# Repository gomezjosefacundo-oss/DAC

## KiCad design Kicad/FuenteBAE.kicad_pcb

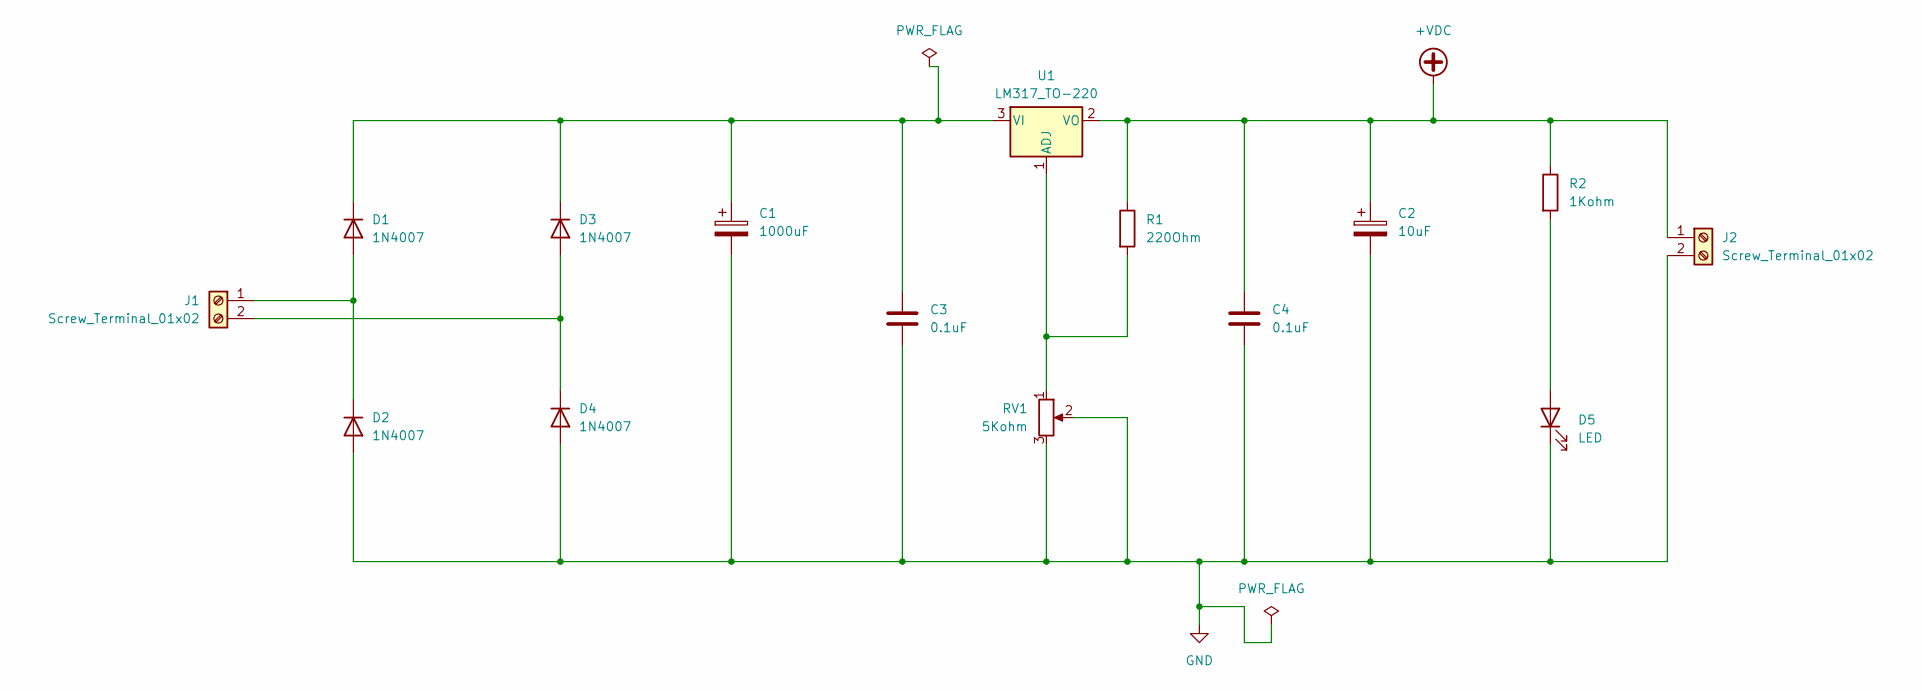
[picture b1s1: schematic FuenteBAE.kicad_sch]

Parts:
C1: 1000uF; CP_Radial_D10.0mm_P2.50mm
C2: 10uF; CP_Radial_D4.0mm_P2.00mm
C3, C4: 0.1uF; C_Disc_D4.7mm_W2.5mm_P5.00mm
D1, D2, D3, D4: 1N4007; D_DO-41_SOD81_P10.16mm_Horizontal
D5: LED; LED_D5.0mm
J1, J2: Screw_Terminal_01x02; Altech_AK300_1x02_P5.00mm_45-Degree
R1: 220Ohm; R_Axial_DIN0207_L6.3mm_D2.5mm_P10.16mm_Horizontal
R2: 1Kohm; R_Axial_DIN0207_L6.3mm_D2.5mm_P10.16mm_Horizontal
RV1: 5Kohm; Potentiometer_Bourns_3296W_Vertical
U1: LM317_TO-220; TO-220-3_Vertical

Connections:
+VDC: C2.1, C4.1, J2.1, R1.1, R2.1, U1.2 (VO)
GND: C1.2, C2.2, C3.2, C4.2, D2.2 (A), D4.2 (A), D5.1 (K), J2.2, RV1.2, RV1.3
unnamed: D1.2 (A), D2.1 (K), J1.1
unnamed: C1.1, C3.1, D1.1 (K), D3.1 (K), U1.3 (VI)
unnamed: D3.2 (A), D4.1 (K), J1.2
unnamed: D5.2 (A), R2.2
unnamed: R1.2, RV1.1, U1.1 (ADJ)

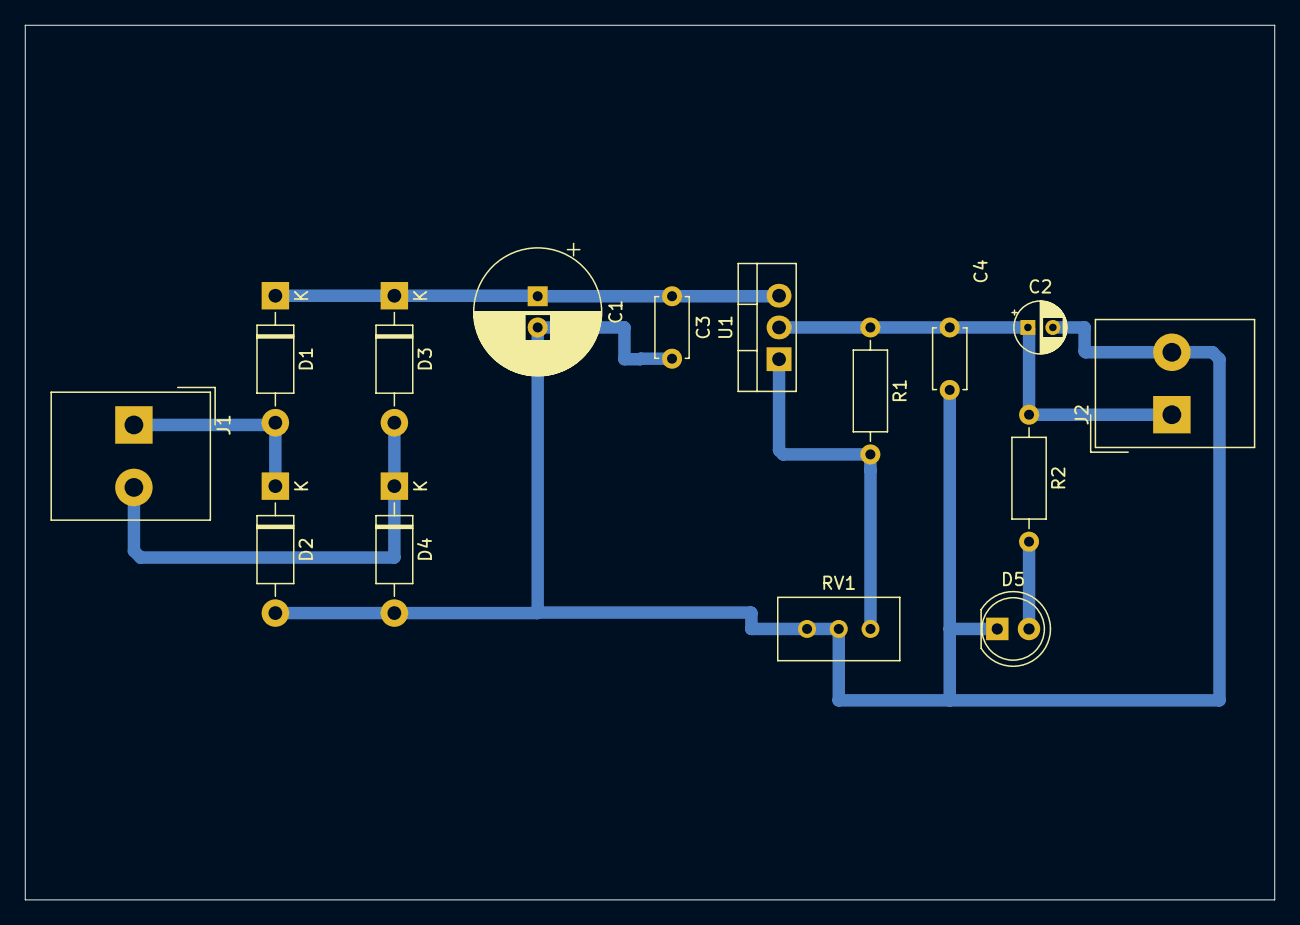
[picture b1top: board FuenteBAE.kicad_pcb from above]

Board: 2 copper layers, 100.0 x 70.0 mm, 15 parts (0 on the bottom side), 7 nets.

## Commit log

2025-10-02 Create a
2025-10-02 Create dummy
2025-10-02 Update and rename fp-info-cache to Kicad/fp-info-cache
2025-10-02 Rename ~FuenteBAE.kicad_pcb.lck to Kicad/~FuenteBAE.kicad_pcb.lck
2025-10-02 Rename ~FuenteBAE.kicad_sch.lck to Kicad/~FuenteBAE.kicad_sch.lck
